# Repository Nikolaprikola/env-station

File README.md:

# ESP32-C3 Environmental Monitoring Station

Dvoslojna PCB za mjerenje temperature, vlage, tlaka, CO2 i
cestica. Prvi vlastiti PCB dizajn.

## Hardver
- ESP32-C3-WROOM-02
- AP2112K-3.3 LDO, napajanje preko USB-C
- I2C header (BME280, SCD40)
- UART header (PMS5003)
- Boot i reset tipke

## Status
Rev A - dizajn zavrsen, DRC cist, ploca jos nije proizvedena.

## Alati
KiCad 10

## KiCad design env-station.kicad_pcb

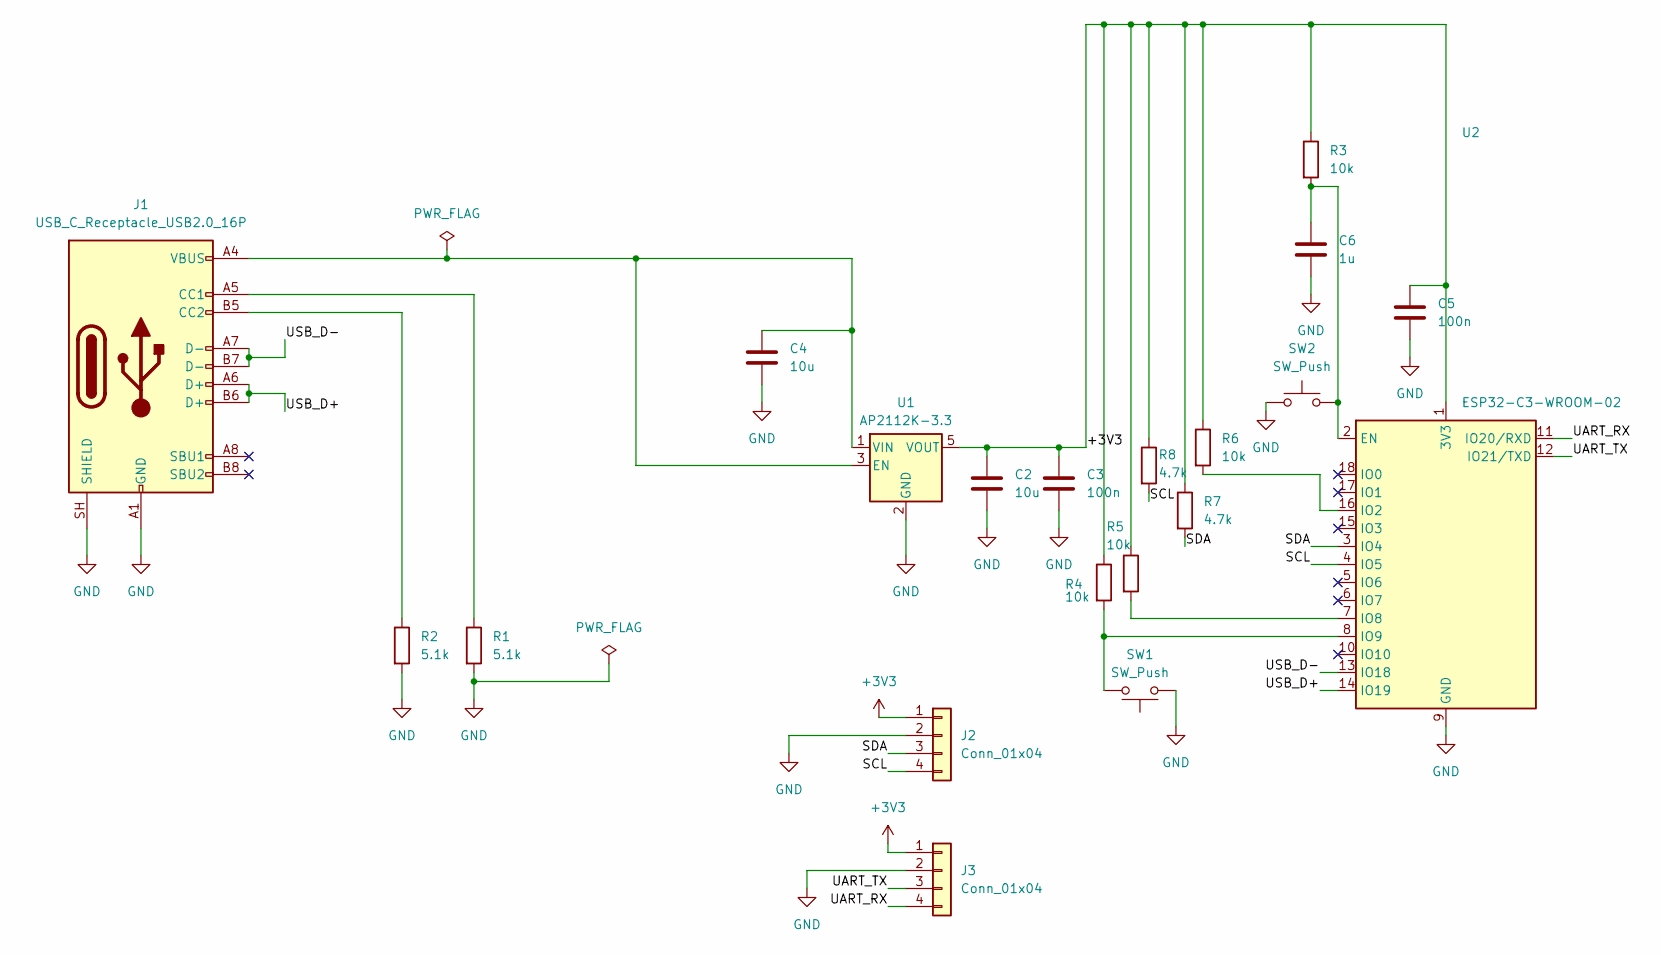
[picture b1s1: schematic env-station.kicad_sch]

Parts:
C2, C4: 10u; C_0805_2012Metric
C3, C5: 100n; C_0805_2012Metric
C6: 1u; C_0805_2012Metric
J1: USB_C_Receptacle_USB2.0_16P; USB_C_Receptacle_HRO_TYPE-C-31-M-12
J2, J3: Conn_01x04; PinHeader_1x04_P2.54mm_Vertical
R1, R2: 5.1k; R_0805_2012Metric
R3, R4, R5, R6: 10k; R_0805_2012Metric
R7, R8: 4.7k; R_0805_2012Metric
SW1, SW2: SW_Push; SW_SPST_TL3342
U1: AP2112K-3.3; SOT-23-5
U2: ESP32-C3-WROOM-02

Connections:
+3V3: C2.1, C3.1, C5.1, J2.1, J3.1, R3.1, R4.1, R5.1, R6.1, R7.1, R8.1, U1.5 (VOUT), U2.1 (3V3)
/SCL: J2.4, R8.2, U2.4 (IO5)
/SDA: J2.3, R7.2, U2.3 (IO4)
/UART_RX: J3.4, U2.11 (IO20/RXD)
/UART_TX: J3.3, U2.12 (IO21/TXD)
/USB_D+: J1.A6 (D+), J1.B6 (D+), U2.14 (IO19)
/USB_D-: J1.A7 (D-), J1.B7 (D-), U2.13 (IO18)
GND: C2.2, C3.2, C4.2, C5.2, C6.2, J1.A1 (GND), J1.A12 (GND), J1.B1 (GND), J1.B12 (GND), J1.SH (SHIELD), J2.2, J3.2, R1.2, R2.2, SW1.1, SW2.1, U1.2 (GND), U2.9 (GND), U2.19 (GND)
unnamed: J1.A5 (CC1), R1.1
unnamed: J1.B5 (CC2), R2.1
unnamed: C4.1, J1.A4 (VBUS), J1.A9 (VBUS), J1.B4 (VBUS), J1.B9 (VBUS), U1.1 (VIN), U1.3 (EN)
unnamed: C6.1, R3.2, SW2.2, U2.2 (EN)
unnamed: R6.2, U2.16 (IO2)
unnamed: R5.2, U2.7 (IO8)
unnamed: R4.2, SW1.2, U2.8 (IO9)

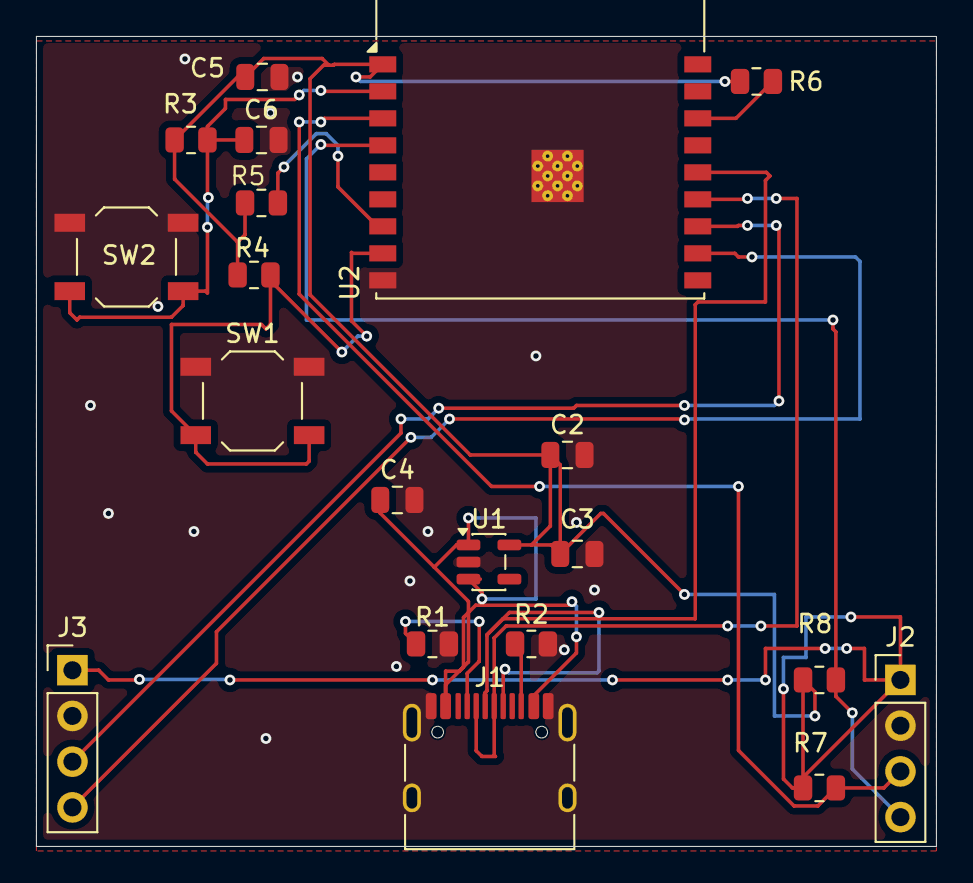
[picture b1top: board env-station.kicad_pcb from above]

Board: 2 copper layers, 50.0 x 45.0 mm, 20 parts (0 on the bottom side), 15 nets.
